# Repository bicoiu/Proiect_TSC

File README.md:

# TSC-Project

## BOM (Bill Of Materials)

| Component             | Supplier Link                                                                                             | Datasheet                                                                                         |
|-----------------------|-----------------------------------------------------------------------------------------------------------|----------------------------------------------------------------------------------------------------|
| 112A-TAAR-R03         | [Model](https://store.comet.srl.ro/Catalogue/Product/43497/)                                             | [Datasheet](https://www.snapeda.com/parts/112A-TAAR-R03/Attend/datasheet/)                        |
| 744043680             | [Model](https://ro.mouser.com/ProductDetail/Wurth-Elektronik/744043680?qs=PGXP4M47uW6VkZq%252BkzjrHA%3D%3D)| [Datasheet](https://www.we-online.com/components/products/datasheet/744043680.pdf)                |
| BD5229G-TR            | [Model](https://componentsearchengine.com/part-view/BD5229G-TR/ROHM%20Semiconductor)                     | [Datasheet](https://fscdn.rohm.com/en/products/databook/datasheet/ic/power/voltage_detector/bd52xxg-e.pdf) |
| Capacitor 0402        | [Model](https://ro.mouser.com/c/passive-components/capacitors/ceramic-capacitors/?q=CC0402&srsltid=AfmBOoogjqwwed3xvp6V5-bfVkRuawirfMcnAC47L-UQdC3mnXJk097M) | [Datasheet](https://componentsearchengine.com/Datasheets/2/CC0402MRX5R5BB106.pdf)                  |
| CPH3225A              | [Model](https://www.snapeda.com/parts/CPH3225A/Seiko+Instruments/view-part/?ref=snap)                    | [Datasheet](https://www.snapeda.com/parts/CPH3225A/Seiko%20Instruments/datasheet/)                |
| Custom Button         | [Model](https://industry.panasonic.com/global/en/products/control/switch/light-touch/number/evqpuj02k)    | [Datasheet](https://industry.panasonic.com/global/en/downloads?tab=catalog&small_g_cd=203&part_no=EVQPUJ02K) |
| DS3231SN              | [Model](https://www.snapeda.com/parts/DS3231SN%23/Analog+Devices/view-part/?ref=eda)                    | [Datasheet](https://www.snapeda.com/parts/DS3231SN%23/Analog%20Devices/datasheet/)                |
| ESP32 WROVER 0805 Capacitor | [Model](https://componentsearchengine.com/part-view/ESP32-WROVER-IB/Espressif%20Systems)          | [Datasheet](https://4donline.ihs.com/images/VipMasterIC/IC/ESPS/ESPS-S-A0016256762/ESPS-S-A0016256762-1.pdf?hkey=EF798316E3902B6ED9A73243A3159BB0)                                                                                      |
| ESP32 WROVER BME680 Sensor | [Model](https://www.snapeda.com/parts/BME680/Bosch/view-part/?welcome=home)                        | [Datasheet](https://www.bosch-sensortec.com/media/boschsensortec/downloads/datasheets/bst-bme680-ds001.pdf) |
| ESP32 WROVER MCP73831 Power Management | [Model](https://www.snapeda.com/parts/BME680/Bosch/view-part/?welcome=home)             | [Datasheet](https://www.snapeda.com/parts/MCP73831T-2ACI/OT/Microchip/datasheet/)                  |
| ESP32C6 Varistor 1812 | [Model](https://componentsearchengine.com/part-view/ESP32-C6-MINI-1-H4/Espressif%20Systems)           | [Datasheet](https://4donline.ihs.com/images/VipMasterIC/IC/ESPS/ESPS-S-A0018537656/ESPS-S-A0018537656-1.pdf?hkey=EF798316E3902B6ED9A73243A3159BB0)                                                                                      |
| ESP32C6 WROOM-1-N8    | [Model](https://www.snapeda.com/parts/ESP32-C6-WROOM-1-N8/Espressif+Systems/view-part/?ref=eda)         | [Datasheet](https://www.snapeda.com/parts/ESP32-C6-WROOM-1-N8/Espressif%20Systems/datasheet/)      |
| FH34SRJ-24S-0.5SH     | [Model](https://ro.mouser.com/ProductDetail/Hirose-Connector/FH34SRJ-24S-0.5SH99?qs=vcbW%252B4%252BSTIpKBl5ap9J8Fw%3D%3D) | [Datasheet](https://www.snapeda.com/parts/FH34SRJ-24S-0.5SH(99)/Hirose%20Connector/datasheet/)    |
| LED Chip 0603         | [Model](https://www.snapeda.com/parts/KP-1608SURCK/Kingbright/view-part/?ref=search&t=LED%200603)        | [Datasheet](https://www.snapeda.com/parts/KP-1608SURCK/Kingbright/datasheet/)                     |
| MAX17048G+T10         | [Model](https://www.snapeda.com/parts/MAX17048G+T10/Analog+Devices/view-part/?ref=eda)                  | [Datasheet](https://www.snapeda.com/parts/MAX17048G+T10/Analog%20Devices/datasheet/)              |
| MBR0530 Schottky Diode| [Model](https://www.snapeda.com/parts/MBR0530/Onsemi/view-part/?ref=snap)                               | [Datasheet](https://www.snapeda.com/parts/MBR0530/ON%20Semiconductor/datasheet/)                   |
| PGB1010603MR          | [Model](https://www.snapeda.com/parts/PGB1010603MR/Littelfuse/view-part/?ref=eda)                       | [Datasheet](https://www.snapeda.com/parts/PGB1010603MR/Littelfuse%20Inc./datasheet/)               |
| QWIIC Connector       | [Model](https://www.snapeda.com/parts/PRT-14417/SparkFun/view-part/)                                    | [Datasheet](https://www.snapeda.com/parts/PRT-14417/SparkFun%20Electronics/datasheet/)             |
| RCL CPOL 3528         | [Model](https://www.snapeda.com/parts/CPH3225A/Seiko+Instruments/view-part/?ref=eda)                    | [Datasheet](https://s3.amazonaws.com/snapeda/datasheet/TAJB475K025RNJ_AVX.pdf)                     |
| Resistor 0402         | [Model](https://grabcad.com/library/resistor-0402-1)                                                     | [Datasheet](https://www.yageo.com/upload/media/product/products/datasheet/rchip/PYu-RC_Group_51_RoHS_L_12.pdf) |
| SI1308EDL-T1-GE3 MOSFET | [Model](https://www.snapeda.com/parts/SI1308EDL-T1-GE3/Vishay+Siliconix/view-part/?welcome=home&ref=eda) | [Datasheet](https://www.snapeda.com/parts/SI1308EDL-T1-GE3/Vishay%20Siliconix/datasheet/)         |
| SJ                    | [Model](https://grabcad.com/library/solder-jumpers-1)                                                    | [Datasheet]()                                                                                      |
| USB4110-GF-A          | [Model](https://componentsearchengine.com/part-view/USB4110-GF-A/GCT%20(GLOBAL%20CONNECTOR%20TECHNOLOGY))| [Datasheet](https://gct.co/files/drawings/usb4110.pdf)                                             |
| USBLC6-2SC6Y          | [Model](https://www.snapeda.com/parts/USBLC6-2SC6Y/STMicroelectronics/view-part/?welcome=home&ref=eda)  | [Datasheet](https://www.snapeda.com/parts/USBLC6-2SC6Y/STMicroelectronics/datasheet/)              |
| W25Q512JVEIQ          | [Model](https://www.snapeda.com/parts/W25Q512JVEIQ/Winbond+Electronics/view-part/?ref=eda)              | [Datasheet](https://www.winbond.com/resource-files/W25Q512JV%20SPI%20RevB%2006252019%20KMS.pdf)    |
| XC6220A331MR-G        | [Model](https://componentsearchengine.com/part-view/XC6220A331MR-G/Torex)                                | [Datasheet](https://product.torexsemi.com/system/files/series/xc6220.pdf)                          |

## Hardware Description

1. **Microcontroller - ESP32-C6-WROOM-1-N8**  
   - Architecture: RISC-V 32-bit  
   - Clock Speed: 160 MHz  
   - Wireless Connectivity: 2.4 GHz Wi-Fi 6, Bluetooth 5.0  

2. **Power Management & Battery**  
   - Battery Type: Li-Po (Lithium Polymer), 3.7V, 1800mAh  
   - Charging Circuit: MCP73831T  
   - Input Voltage: 5V via USB-C  
   - Protection Features: Overcharge and deep discharge protection  
   - Voltage Regulator: LDO regulator for stable 3.3V supply  

3. **Display - E-Paper (E-Ink)**  
   - Size: 7.5 inches  
   - Resolution: 800x480 pixels  
   - Interface: SPI  

4. **SD Card Module**  
   - Type: MicroSD (FAT32 supported)  
   - Interface: SPI  

5. **External NOR Flash**  
   - Capacity: 64MB  
   - Interface: SPI  

6. **Environmental Sensor - BME688**  
   - Senses temperature, humidity, pressure, and gas  
   - Interface: I2C  

7. **Real-Time Clock (RTC) - DS3231SN**  
   - Maintains accurate time/date  
   - Interface: I2C  

8. **USB-C Connector & ESD Protection**  
   - Power input and data transfer  
   - ESD protection and Schottky diode for reverse polarity  

9. **Buttons & User Input**  
   - Tactile push buttons  

10. **Communication Interfaces**  
   - GPIO, SPI, I2C, UART, Wi-Fi, Bluetooth  

## Power Consumption Estimation

| Component                | Current Draw (mA) | Voltage (V) | Power (mW) |
|--------------------------|------------------|-------------|------------|
| ESP32-C6 (Wi-Fi active)  | 200              | 3.3         | 660        |
| E-Paper Display (Updating) | 40             | 3.3         | 132        |
| BME688 Sensor (Measuring)  | 3.1            | 3.3         | 10.23      |
| RTC Module (Active)      | 0.15            | 3.3         | 0.495      |
| SD Card (Active)         | 50              | 3.3         | 165        |
| External NOR Flash       | 25              | 3.3         | 82.5       |
| **Total**                | ~318.5mA        | 3.3         | ~1050.72   |

## ESP32-C6 Pin Mapping

| Component                      | ESP32-C6 Pins                           | Interface | Purpose                                                    |
|--------------------------------|-----------------------------------------|----------|------------------------------------------------------------|
| **E-Paper Display**            | IO7 (MOSI), IO6 (SCK), IO10 (CS), IO5 (DC), IO23 (RST), IO3 (BUSY) | SPI  | Transfers image data and controls e-paper state           |
| **MicroSD Card**               | IO7 (MOSI), IO6 (SCK), IO4 (SS_SD), IO2 (MISO)                   | SPI  | Storage and retrieval of e-books                          |
| **Environmental Sensor (BME688)** | IO21 (SDA), IO22 (SCL)                | I2C      | Reads temperature, humidity, pressure, and gas levels     |
| **RTC Module (DS3231)**        | IO21 (SDA), IO22 (SCL), IO18 (RST), IO1 (32KHz), IO0 (INT_RTC)    | I2C      | Maintains time tracking when system is off                |
| **External NOR Flash**         | IO11 (CS), IO6 (SCK), IO2 (MISO), IO7 (MOSI)                      | SPI  | Additional storage for data                               |
| **Battery Monitoring**         | IO21 (SDA), IO22 (SCL)                | I2C      | Reads battery voltage and charge status                   |
| **USB-C Connection**           | GPIOs via voltage regulation           | USB      | Powers and programs the ESP32-C6                          |
| **Control Buttons**            | IO9 (BOOT), IO15 (CHANGE), EN (RESET)  | GPIO     | User input for device interactions                        |

## Additional Design Notes

### Footprint Adjustments
- **Diode (SMD-Hole)**: The original footprint had pad holes too small for reliable soldering. Pads were updated to 35mil x 190mil.  
- **U4 – MAX17048G+T10**: VBAT power trace width was 0.3mm, while pin widths were only 0.27mm. Adjusted pin size to match trace width.

### Routing & Ground Plane
- Power traces are on the top layer; ~150 vias used for bottom-layer signals.  
- Ground plane on both top and bottom layers for low-impedance grounding and reduced EMI.

### Component Placement
- External ports align with the OpenBook enclosure for accessibility.  
- Test pads near board edges for easy debugging.  
- 100nF decoupling capacitors placed close to IC power pins for noise reduction.

### Schematic & 3D Model Issues
- A net named GND1 appeared but was not functional; removed after review.  
- 3D model updates caused pin order reversals for certain 2-pin components, fixed by rotating 180 degrees.

### Enclosure & 3D Integration
- An alternative enclosure was tested with a custom color.  
- 3D components were imported via two methods depending on their usage frequency.

### Difficulties Encountered
- Am intampinat dificultati la realizarea schematicului pana am inceput sa ma documentez.  
- In etapa de proiectare PCB, cea mai mare provocare a fost sa asez toate componentele in dimensiunile cerute.  
- Rutarea finala a fost de asemenea dificila, necesitand mai multe iteratii pentru a organiza corespunzator toate traseele.

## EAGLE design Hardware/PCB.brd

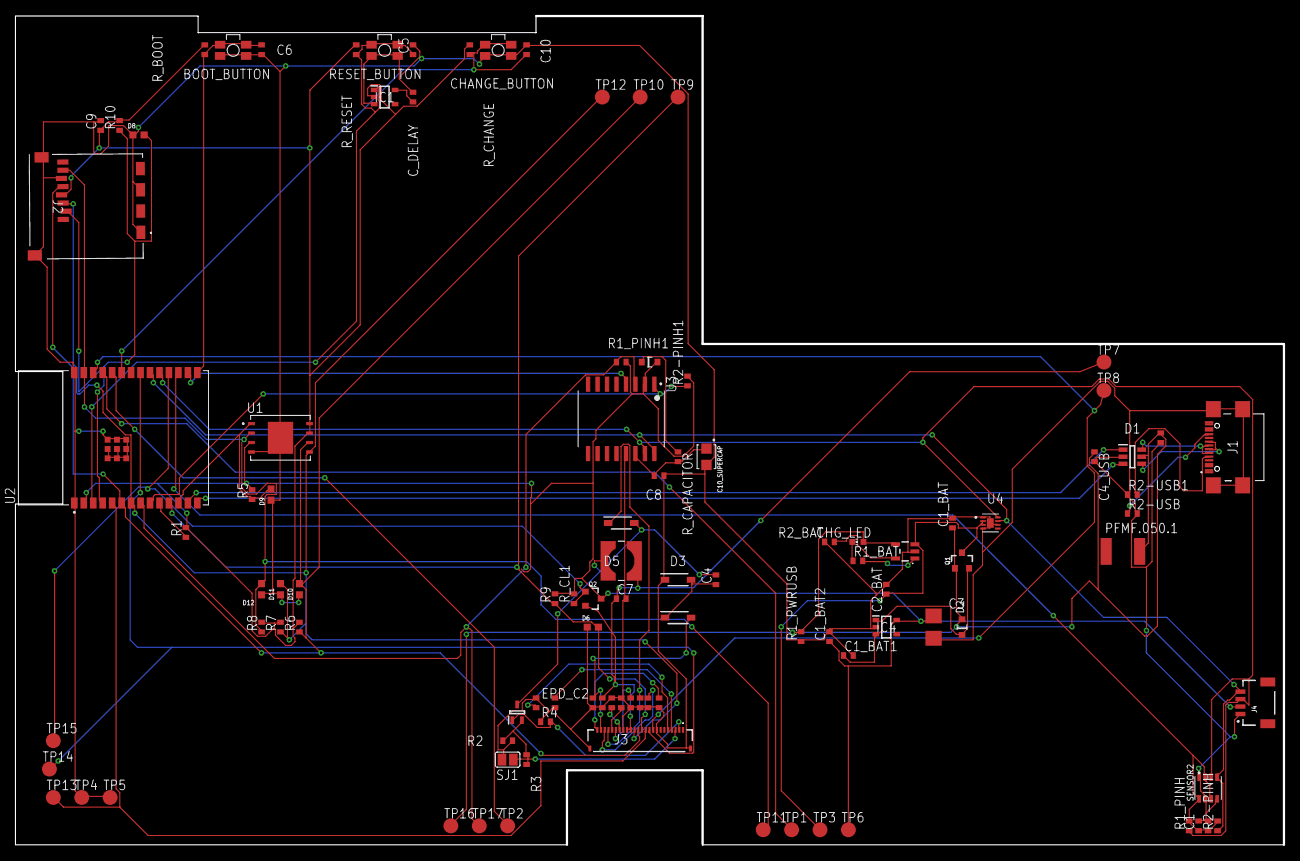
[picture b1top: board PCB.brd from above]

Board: 2 copper layers, 170.2 x 111.2 mm, 103 parts (0 on the bottom side), 54 nets.

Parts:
BOOT_BUTTON: BUTTON_CUSYOMV1; MYBUTTON
C1, C2, C6, C8, C10: 100nF; EAGLE-LTSPICE_C0402
C1_BAT, C5_USB: 4.7uF; ESP32_WROVER_EAGLE-LTSPICE_C0402
C1_BAT1, C1_BAT2, C2_BAT: 4.7uF; EAGLE-LTSPICE_C0402
C3: 100uF; RCL_CT3528
C4: 4.7uF/25V; EAGLE-LTSPICE_C0402
C4_USB, C9: 100nF; ESP32_WROVER_EAGLE-LTSPICE_C0402
C5: 1uF; EAGLE-LTSPICE_C0402
C7: 10uF; EAGLE-LTSPICE_C0402
C10_SUPERCAP: CPH3225A; CAPCP3225X100N
CHANGE_BUTTON: BUTTON_CUSYOMV1; MYBUTTON
CHG_LED: ADAFRUIT_CHIP-LED0603
C_DELAY: 100nF; EAGLE-LTSPICE_C0402
D1: USBLC6-2SC6Y; SOT95P280X145-6N
D2, D7: ESP32_WROVER_AVX---SD0805S020S1R0_AVX_SD0805S020S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; ESP32_WROVER_AVX---SD0805S020S1R0_AVX_SD0805S020S1R0_0
D3, D4, D5: MBR0530; SOD3716X135N
D6, D8, D9, D10, D11, D12: PGB1010603MR; DIOC1608X36N
EPD_C1, EPD_C2, EPD_C5, EPD_C6, EPD_C7, EPD_C8, EPD_C9, EPD_C11, EPD_C12: 1uF/50V; EAGLE-LTSPICE_C0402
EPD_C10: EAGLE-LTSPICE_C0402
IC1: BD5229G-TR; SOT95P280X125-5N
IC4: XC6220A331MR-G; SOT95P280X120-5N
J1: SAMACSYS_PARTS_USB4110-GF-A; SAMACSYS_PARTS_USB4110GFA
J2: 112A-TAAR-R03_ATTEND; 112ATAARR03ATTEND
J3: FH34SRJ-24S-0.5SH_99_; FH34SRJ24S05SH99
J4: QWIIC_RIGHT_ANGLE; JST04_1MM_RA
L1: 744043680IND_4828-WE-TPC_WRE; IND_4828-WE-TPC_WRE
MCP73831: ESP32_WROVER_SPARKFUN-IC-POWER_MCP73831; ESP32_WROVER_SPARKFUN-IC-POWER_SOT23-5
PFMF.050.1: ESP32C6_VARISTORCN1812; ESP32C6_VARISTOR_CT/CN1812
Q1, Q2: 20V/4.2A/52mΩ/1.4W; ESP32_WROVER_SPARKFUN-DISCRETESEMI_SOT23-3
Q3: SI1308EDL-T1-GE3; SOT65P210X110-3N
R1, R4: 10K; ESP32_WROVER_EAGLE-LTSPICE_R0402
R1_BAT: 200; ESP32_WROVER_EAGLE-LTSPICE_R0402
R1_PINH, R1_PINH1, R2-PINH, R2-PINH1, R5, R6, R7, R8, R9, R10: 10k; ESP32_WROVER_EAGLE-LTSPICE_R0402
R1_PWRUSB: 100k; ESP32_WROVER_EAGLE-LTSPICE_R0402
R2: 2.2; ESP32_WROVER_EAGLE-LTSPICE_R0402
R2-USB, R2-USB1: 5k1; ESP32_WROVER_EAGLE-LTSPICE_R0402
R2_BAT: 2k; ESP32_WROVER_EAGLE-LTSPICE_R0402
R3: 0.47; ESP32_WROVER_EAGLE-LTSPICE_R0402
RESET_BUTTON: BUTTON_CUSYOMV1; MYBUTTON
R_BOOT: 10k; ESP32_WROVER_EAGLE-LTSPICE_R0402
R_CAPACITOR: 15; ESP32_WROVER_EAGLE-LTSPICE_R0402
R_CHANGE: 10k; ESP32_WROVER_EAGLE-LTSPICE_R0402
R_CL1: 10k; ESP32_WROVER_EAGLE-LTSPICE_R0402
R_RESET: 10k; ESP32_WROVER_EAGLE-LTSPICE_R0402
SENSOR2: ESP32_WROVER_BME680_BME680; ESP32_WROVER_BME680_PSON80P300X300X100-8N
SJ1: SJ
TP1, TP2, TP3, TP4, TP5, TP6, TP7, TP8, TP9, TP10, TP11, TP12, TP13, TP14, TP15, TP16, TP17: TPTP20R; TP20R
U1: W25Q512JVEIQ; SON127P600X800X80-9N
U2: ESP32-C6-WROOM-1-N8; XCVR_ESP32-C6-WROOM-1-N8
U3: DS3231SN#; SOIC127P1032X265-16N
U4: MAX17048G+T10; SON50P200X200X80-9N

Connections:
3V3: C1_BAT2.1, C3.+, C9.1, D7.2, IC1.2, IC4.5, J2.P4, J4.2, Q2.3, R1.2, R1_PINH1.2, R2-PINH1.2, R5.2, R6.2, R7.2, R8.2, R9.2, R10.2, R_BOOT.2, R_CHANGE.2, R_CL1.2, R_RESET.2, TP6.TP, U1.3, U1.7, U1.8, U2.2, U3.2
32KHZ: R2-PINH1.1, U2.9, U3.1
DN: D1.6, J1.A7, J1.B7
DP: D1.4, J1.A6, J1.B6
EPD_3V3: C7.1, EPD_C5.2, J3.15, J3.16, L1.2, Q2.2, TP7.TP
EPD_3V3_C: Q2.1, R_CL1.1, TP15.TP, U2.18
EPD_BUSY: J3.9, TP8.TP, U2.26
EPD_CS: D6.2, J3.12, R9.1, TP9.TP, U2.11
EPD_DC: J3.11, TP13.TP, U2.5
EPD_RST: J3.10, TP14.TP, U2.21
FLASH_CS: D9.2, R5.1, U1.1, U2.12
GDR: J3.2, Q3.1, R4.2
GND: BOOT_BUTTON.1, BOOT_BUTTON.2, C1.2, C1_BAT.2, C1_BAT1.2, C1_BAT2.2, C2.2, C2_BAT.2, C3.-, C4_USB.2, C5.2, C5_USB.2, C6.2, C7.2, C8.2, C9.2, C10.2, C10_SUPERCAP.2, CHANGE_BUTTON.1, CHANGE_BUTTON.2, C_DELAY.2, D1.2, D3.1, D6.1, D8.1, D9.1, D10.1, D11.1, D12.1, EPD_C1.1, EPD_C2.1, EPD_C5.1, EPD_C6.1, EPD_C7.1, EPD_C8.1, EPD_C9.1, EPD_C10.1, EPD_C11.1, EPD_C12.1, IC1.3, IC4.2, J1.A1, J1.A12, J1.B1, J1.B12, J1.MP1, J1.MP2, J1.MP3, J1.MP4, J2.G1, J2.G2, J2.G3, J2.G4, J2.P6, J3.8, J3.17, J3.MP1, J3.MP2, J4.1, MCP73831.2, R1_PWRUSB.1, R2.1, R2-USB.2, R2-USB1.1, R2_BAT.1, R4.1, RESET_BUTTON.1, RESET_BUTTON.2, SENSOR2.1, SENSOR2.5, SENSOR2.7, SJ1.1, TP4.TP, TP5.TP, U1.4, U1.9, U2.1, U2.28, U2.29_1, U2.29_2, U2.29_3, U2.29_4, U2.29_5, U2.29_6, U2.29_7, U2.29_8, U2.29_9, U3.13, U4.1, U4.4, U4.6, U4.9
GPIO8: R1.1, U2.10
I2C_PW: C1.1, C2.1, R1_PINH.2, R2-PINH.2, SENSOR2.2, SENSOR2.6, SENSOR2.8, U2.17
INT_RTC: R1_PINH1.1, TP17.TP, U2.8, U3.3
IO/BOOT: BOOT_BUTTON.3, BOOT_BUTTON.4, C6.1, R_BOOT.1, U2.15
IO/CHANGE: C10.1, CHANGE_BUTTON.3, CHANGE_BUTTON.4, R_CHANGE.1, U2.23
MISO: D12.2, J2.P7, R8.1, TP11.TP, U1.2, U2.27
MOSI: D11.2, J2.P3, J3.14, R7.1, TP12.TP, U1.5, U2.7
unnamed: C_DELAY.1, IC1.5
unnamed: J1.B5, R2-USB.1
unnamed: J1.A5, R2-USB1.2
unnamed: C1_BAT1.1, D2.1, IC4.1, IC4.3, Q1.2
unnamed: C4.1, D3.2, D4.1
unnamed: MCP73831.1, R1_BAT.2
unnamed: CHG_LED.C, R1_BAT.1
unnamed: MCP73831.5, R2_BAT.2
unnamed: EPD_C1.2, J3.4
unnamed: EPD_C2.2, J3.5
unnamed: EPD_C12.2, J3.24
unnamed: EPD_C10.2, J3.22
unnamed: EPD_C8.2, J3.20
unnamed: EPD_C7.2, J3.19
unnamed: EPD_C6.2, J3.18
unnamed: D7.1, R_CAPACITOR.1
PREVGH: D5.1, EPD_C9.2, J3.21
PREVGL: D4.2, EPD_C11.2, J3.23
RESE: J3.3, Q3.2, R2.2, R3.1, R3.2, SJ1.2
RESET: C5.1, IC1.1, RESET_BUTTON.3, RESET_BUTTON.4, R_RESET.1, U2.3
RTC_RST: U2.16, U3.4
RX: TP2.TP, U2.24
SCK: D10.2, J2.P5, J3.13, R6.1, TP10.TP, U1.6, U2.6
SCL: J4.4, R2-PINH.1, SENSOR2.4, U2.20, U3.16, U4.7
SDA: J4.3, R1_PINH.1, SENSOR2.3, U2.19, U3.15, U4.8
SRC: C4.2, D5.2, L1.1, Q3.3
SS_SD: D8.2, J2.P2, R10.1, U2.4
TX: TP1.TP, U2.25
USB_D+: D1.3, U2.14
USB_D-: D1.1, U2.13
VBAT: C2_BAT.1, MCP73831.3, Q1.3, TP3.TP, U4.2, U4.3
VBUS: C1_BAT.1, C4_USB.1, C5_USB.1, CHG_LED.A, D1.5, D2.2, MCP73831.4, PFMF.050.1.2, Q1.1, R1_PWRUSB.2, TP16.TP
VRTC: C8.1, C10_SUPERCAP.1, R_CAPACITOR.2, U3.14
VUSB: J1.A4, J1.A9, J1.B4, J1.B9, PFMF.050.1.1

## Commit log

2025-04-09 new file: Hardware/OpenBook.sch new file: Hardware/PCB.brd new file: Hardware/board.png new file: Hardware/gerber.zip new file: Images/bord.png new file: Manufacturing/BOM.csv new file: README.md com
2025-04-09 Update LICENSE
2025-04-15 Fixed shorted GND on PIN21
2025-04-15 Fixed TX pin disconnection
2025-04-15 Fixed 90 degree routes
2025-04-15 Silkscreen Text overlapping

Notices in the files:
parts and their libraries:
COPYRIGHT: Copyright (C) 2024 Ultra Librarian. All rights reserved.
